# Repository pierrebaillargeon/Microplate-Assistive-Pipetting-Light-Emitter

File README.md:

# Microplate Assistive Pipetting Light Emitter

The contents of this repository represent the design files and code needed to reproduce the electronics, firmware and GUI interface for the Microplate Assistive Pipetting Light Emitter. 

A manuscript describing the design and usage of this light guide has been published in the <A href="https://journals.sagepub.com/doi/full/10.1177/2472630318822476">SLAS Technology journal</A> and presented at SLAS 2019 as part of a presentation titled <A href="https://www.pathlms.com/slas/courses/10547/video_presentations/127546">'A longitudinal analysis over 10 years of enabling technologies for early drug discovery using open source tools'</a>.

If you are interested in purchasing preassembled illumination panels, as opposed to assembling them by hand, they are available on the <a href="https://www.tindie.com/stores/Maplebear/">Maplebear Electronics Tindie store</a>.

<A href="https://raw.githubusercontent.com/pierrebaillargeon/Microplate-Assistive-Pipetting-Light-Emitter/master/Electronics/Documentation/96-well_RGB_light_Guide_v1.0-with_microplate.jpg"></a>
  
<A href="https://raw.githubusercontent.com/pierrebaillargeon/Microplate-Assistive-Pipetting-Light-Emitter/master/Electronics/Documentation/96-well_RGB_light_guide_v1.3-prototype_PCB.png"></a>
  
<A href="https://raw.githubusercontent.com/pierrebaillargeon/Microplate-Assistive-Pipetting-Light-Emitter/master/Electronics/Documentation/384-well_RGB_light_guide_v1.1.png"></a>

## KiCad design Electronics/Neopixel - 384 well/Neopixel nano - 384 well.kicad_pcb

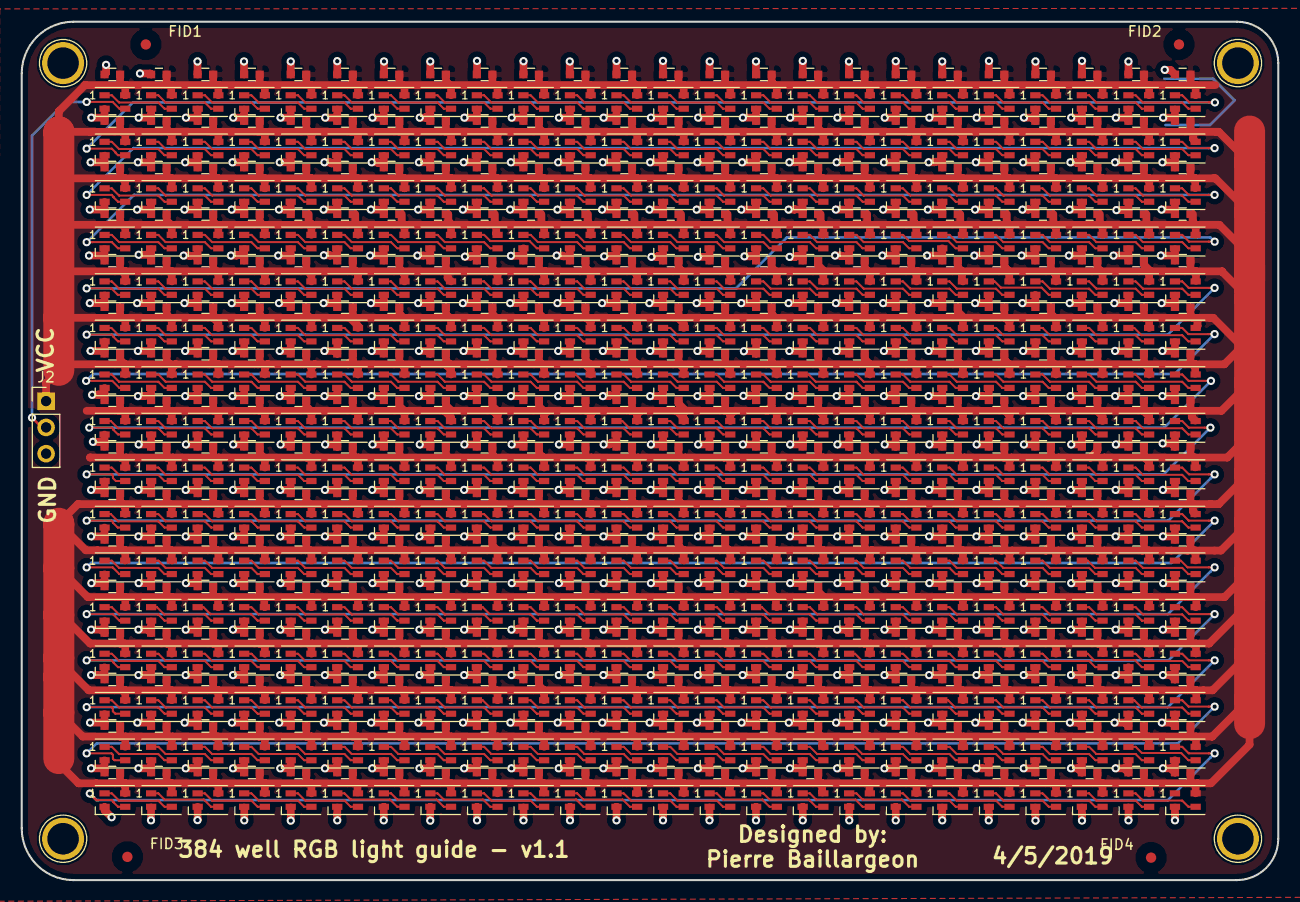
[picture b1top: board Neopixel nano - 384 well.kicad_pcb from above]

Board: 2 copper layers, 121.5 x 83.0 mm, 773 parts (0 on the bottom side), 386 nets.

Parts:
C1, C2, C3, C4, C5, C6, C7, C8, C9, C10, C11, C12, C13, C14, C15, C16, C17, C18, C19, C20, C21, C22, C23, C24, C25, C26, C27, C28, C29, C30, C31, C32, C33, C34, C35, C36, C37, C38, C39, C40, C41, C42, C43, C44, C45, C46, C47, C48, C49, C50, C51, C52, C53, C54, C55, C56, C57, C58, C59, C60, C61, C62, C63, C64, C65, C66, C67, C68, C69, C70, C71, C72, C73, C74, C75, C76, C77, C78, C79, C80, C81, C82, C83, C84, C85, C86, C87, C88, C89, C90, C91, C92, C93, C94, C95, C96, C97, C98, C99, C100, C101, C102, C103, C104, C105, C106, C107, C108, C109, C110, C111, C112, C113, C114, C115, C116, C117, C118, C119, C120, C121, C122, C123, C124, C125, C126, C127, C128, C129, C130, C131, C132, C133, C134, C135, C136, C137, C138, C139, C140, C141, C142, C143, C144, C145, C146, C147, C148, C149, C150, C151, C152, C153, C154, C155, C156, C157, C158, C159, C160, C161, C162, C163, C164, C165, C166, C167, C168, C169, C170, C171, C172, C173, C174, C175, C176, C177, C178, C179, C180, C181, C182, C183, C184, C185, C186, C187, C188, C189, C190, C191, C192, C193, C194, C195, C196, C197, C198, C199, C200, C201, C202, C203, C204, C205, C206, C207, C208, C209, C210, C211, C212, C213, C214, C215, C216, C217, C218, C219, C220, C221, C222, C223, C224, C225, C226, C227, C228, C229, C230, C231, C232, C233, C234, C235, C236, C237, C238, C239, C240, C241, C242, C243, C244, C245, C246, C247, C248, C249, C250, C251, C252, C253, C254, C255, C256, C257, C258, C259, C260, C261, C262, C263, C264, C265, C266, C267, C268, C269, C270, C271, C272, C273, C274, C275, C276, C277, C278, C279, C280, C281, C282, C283, C284, C285, C286, C287, C288, C289, C290, C291, C292, C293, C294, C295, C296, C297, C298, C299, C300, C301, C302, C303, C304, C305, C306, C307, C308, C309, C310, C311, C312, C313, C314, C315, C316, C317, C318, C319, C320, C321, C322, C323, C324, C325, C326, C327, C328, C329, C330, C331, C332, C333, C334, C335, C336, C337, C338, C339, C340, C341, C342, C343, C344, C345, C346, C347, C348, C349, C350, C351, C352, C353, C354, C355, C356, C357, C358, C359, C360, C361, C362, C363, C364, C365, C366, C367, C368, C369, C370, C371, C372, C373, C374, C375, C376, C377, C378, C379, C380, C381, C382, C383, C384: CAP; C_0603
D1, D2, D3, D4, D5, D6, D7, D8, D9, D10, D11, D12, D13, D14, D15, D16, D17, D18, D19, D20, D21, D22, D23, D24, D25, D26, D27, D28, D29, D30, D31, D32, D33, D34, D35, D36, D37, D38, D39, D40, D41, D42, D43, D44, D45, D46, D47, D48, D49, D50, D51, D52, D53, D54, D55, D56, D57, D58, D59, D60, D61, D62, D63, D64, D65, D66, D67, D68, D69, D70, D71, D72, D73, D74, D75, D76, D77, D78, D79, D80, D81, D82, D83, D84, D85, D86, D87, D88, D89, D90, D91, D92, D93, D94, D95, D96, D97, D98, D99, D100, D101, D102, D103, D104, D105, D106, D107, D108, D109, D110, D111, D112, D113, D114, D115, D116, D117, D118, D119, D120, D121, D122, D123, D124, D125, D126, D127, D128, D129, D130, D131, D132, D133, D134, D135, D136, D137, D138, D139, D140, D141, D142, D143, D144, D145, D146, D147, D148, D149, D150, D151, D152, D153, D154, D155, D156, D157, D158, D159, D160, D161, D162, D163, D164, D165, D166, D167, D168, D169, D170, D171, D172, D173, D174, D175, D176, D177, D178, D179, D180, D181, D182, D183, D184, D185, D186, D187, D188, D189, D190, D191, D192, D193, D194, D195, D196, D197, D198, D199, D200, D201, D202, D203, D204, D205, D206, D207, D208, D209, D210, D211, D212, D213, D214, D215, D216, D217, D218, D219, D220, D221, D222, D223, D224, D225, D226, D227, D228, D229, D230, D231, D232, D233, D234, D235, D236, D237, D238, D239, D240, D241, D242, D243, D244, D245, D246, D247, D248, D249, D250, D251, D252, D253, D254, D255, D256, D257, D258, D259, D260, D261, D262, D263, D264, D265, D266, D267, D268, D269, D270, D271, D272, D273, D274, D275, D276, D277, D278, D279, D280, D281, D282, D283, D284, D285, D286, D287, D288, D289, D290, D291, D292, D293, D294, D295, D296, D297, D298, D299, D300, D301, D302, D303, D304, D305, D306, D307, D308, D309, D310, D311, D312, D313, D314, D315, D316, D317, D318, D319, D320, D321, D322, D323, D324, D325, D326, D327, D328, D329, D330, D331, D332, D333, D334, D335, D336, D337, D338, D339, D340, D341, D342, D343, D344, D345, D346, D347, D348, D349, D350, D351, D352, D353, D354, D355, D356, D357, D358, D359, D360, D361, D362, D363, D364, D365, D366, D367, D368, D369, D370, D371, D372, D373, D374, D375, D376, D377, D378, D379, D380, D381, D382, D383, D384: SK6805; LED_SK6805_PLCC4_2.4x2.7mm_P1.3mm
FID1, FID2, FID3, FID4: Fiducial_1mm_Mask3mm
J2: Conn_01x03_Male; Pin_Header_Straight_1x03_Pitch2.54mm

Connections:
GND: C1.2, C2.2, C3.2, C4.2, C5.2, C6.2, C7.2, C8.2, C9.2, C10.2, C11.2, C12.2, C13.2, C14.2, C15.2, C16.2, C17.2, C18.2, C19.2, C20.2, C21.2, C22.2, C23.2, C24.2, C25.2, C26.2, C27.2, C28.2, C29.2, C30.2, C31.2, C32.2, C33.2, C34.2, C35.2, C36.2, C37.2, C38.2, C39.2, C40.2, C41.2, C42.2, C43.2, C44.2, C45.2, C46.2, C47.2, C48.2, C49.2, C50.2, C51.2, C52.2, C53.2, C54.2, C55.2, C56.2, C57.2, C58.2, C59.2, C60.2, C61.2, C62.2, C63.2, C64.2, C65.2, C66.2, C67.2, C68.2, C69.2, C70.2, C71.2, C72.2, C73.2, C74.2, C75.2, C76.2, C77.2, C78.2, C79.2, C80.2, C81.2, C82.2, C83.2, C84.2, C85.2, C86.2, C87.2, C88.2, C89.2, C90.2, C91.2, C92.2, C93.2, C94.2, C95.2, C96.2, C97.2, C98.2, C99.2, C100.2, C101.2, C102.2, C103.2, C104.2, C105.2, C106.2, C107.2, C108.2, C109.2, C110.2, C111.2, C112.2, C113.2, C114.2, C115.2, C116.2, C117.2, C118.2, C119.2, C120.2, C121.2, C122.2, C123.2, C124.2, C125.2, C126.2, C127.2, C128.2, C129.2, C130.2, C131.2, C132.2, C133.2, C134.2, C135.2, C136.2, C137.2, C138.2, C139.2, C140.2, C141.2, C142.2, C143.2, C144.2, C145.2, C146.2, C147.2, C148.2, C149.2, C150.2, C151.2, C152.2, C153.2, C154.2, C155.2, C156.2, C157.2, C158.2, C159.2, C160.2, C161.2, C162.2, C163.2, C164.2, C165.2, C166.2, C167.2, C168.2, C169.2, C170.2, C171.2, C172.2, C173.2, C174.2, C175.2, C176.2, C177.2, C178.2, C179.2, C180.2, C181.2, C182.2, C183.2, C184.2, C185.2, C186.2, C187.2, C188.2, C189.2, C190.2, C191.2, C192.2, C193.2, C194.2, C195.2, C196.2, C197.2, C198.2, C199.2, C200.2, C201.2, C202.2, C203.2, C204.2, C205.2, C206.2, C207.2, C208.2, C209.2, C210.2, C211.2, C212.2, C213.2, C214.2, C215.2, C216.2, C217.2, C218.2, C219.2, C220.2, C221.2, C222.2, C223.2, C224.2, C225.2, C226.2, C227.2, C228.2, C229.2, C230.2, C231.2, C232.2, C233.2, C234.2, C235.2, C236.2, C237.2, C238.2, C239.2, C240.2, C241.2, C242.2, C243.2, C244.2, C245.2, C246.2, C247.2, C248.2, C249.2, C250.2, C251.2, C252.2, C253.2, C254.2, C255.2, C256.2, C257.2, C258.2, C259.2, C260.2, C261.2, C262.2, C263.2, C264.2, C265.2, C266.2, C267.2, C268.2, C269.2, C270.2, C271.2, C272.2, C273.2, C274.2, C275.2, C276.2, C277.2, C278.2, C279.2, C280.2, C281.2, C282.2, C283.2, C284.2, C285.2, C286.2, C287.2, C288.2, C289.2, C290.2, C291.2, C292.2, C293.2, C294.2, C295.2, C296.2, C297.2, C298.2, C299.2, C300.2, C301.2, C302.2, C303.2, C304.2, C305.2, C306.2, C307.2, C308.2, C309.2, C310.2, C311.2, C312.2, C313.2, C314.2, C315.2, C316.2, C317.2, C318.2, C319.2, C320.2, C321.2, C322.2, C323.2, C324.2, C325.2, C326.2, C327.2, C328.2, C329.2, C330.2, C331.2, C332.2, C333.2, C334.2, C335.2, C336.2, C337.2, C338.2, C339.2, C340.2, C341.2, C342.2, C343.2, C344.2, C345.2, C346.2, C347.2, C348.2, C349.2, C350.2, C351.2, C352.2, C353.2, C354.2, C355.2, C356.2, C357.2, C358.2, C359.2, C360.2, C361.2, C362.2, C363.2, C364.2, C365.2, C366.2, C367.2, C368.2, C369.2, C370.2, C371.2, C372.2, C373.2, C374.2, C375.2, C376.2, C377.2, C378.2, C379.2, C380.2, C381.2, C382.2, C383.2, C384.2, D1.2, D2.2, D3.2, D4.2, D5.2, D6.2, D7.2, D8.2, D9.2, D10.2, D11.2, D12.2, D13.2, D14.2, D15.2, D16.2, D17.2, D18.2, D19.2, D20.2, D21.2, D22.2, D23.2, D24.2, D25.2, D26.2, D27.2, D28.2, D29.2, D30.2, D31.2, D32.2, D33.2, D34.2, D35.2, D36.2, D37.2, D38.2, D39.2, D40.2, D41.2, D42.2, D43.2, D44.2, D45.2, D46.2, D47.2, D48.2, D49.2, D50.2, D51.2, D52.2, D53.2, D54.2, D55.2, D56.2, D57.2, D58.2, D59.2, D60.2, D61.2, D62.2, D63.2, D64.2, D65.2, D66.2, D67.2, D68.2, D69.2, D70.2, D71.2, D72.2, D73.2, D74.2, D75.2, D76.2, D77.2, D78.2, D79.2, D80.2, D81.2, D82.2, D83.2, D84.2, D85.2, D86.2, D87.2, D88.2, D89.2, D90.2, D91.2, D92.2, D93.2, D94.2, D95.2, D96.2, D97.2, D98.2, D99.2, D100.2, D101.2, D102.2, D103.2, D104.2, D105.2, D106.2, D107.2, D108.2, D109.2, D110.2, D111.2, D112.2, D113.2, D114.2, D115.2, D116.2, D117.2, D118.2, D119.2, D120.2, D121.2, D122.2, D123.2, D124.2, D125.2, D126.2, D127.2, D128.2, D129.2, D130.2, D131.2, D132.2, D133.2, D134.2, D135.2, D136.2, D137.2, D138.2, D139.2, D140.2, D141.2, D142.2, D143.2, D144.2, D145.2, D146.2, D147.2, D148.2, D149.2, D150.2, D151.2, D152.2, D153.2, D154.2, D155.2, D156.2, D157.2, D158.2, D159.2, D160.2, D161.2, D162.2, D163.2, D164.2, D165.2, D166.2, D167.2, D168.2, D169.2, D170.2, D171.2, D172.2, D173.2, D174.2, D175.2, D176.2, D177.2, D178.2, D179.2, D180.2, D181.2, D182.2, D183.2, D184.2, D185.2, D186.2, D187.2, D188.2, D189.2, D190.2, D191.2, D192.2, D193.2, D194.2, D195.2, D196.2, D197.2, D198.2, D199.2, D200.2, D201.2, D202.2, D203.2, D204.2, D205.2, D206.2, D207.2, D208.2, D209.2, D210.2, D211.2, D212.2, D213.2, D214.2, D215.2, D216.2, D217.2, D218.2, D219.2, D220.2, D221.2, D222.2, D223.2, D224.2, D225.2, D226.2, D227.2, D228.2, D229.2, D230.2, D231.2, D232.2, D233.2, D234.2, D235.2, D236.2, D237.2, D238.2, D239.2, D240.2, D241.2, D242.2, D243.2, D244.2, D245.2, D246.2, D247.2, D248.2, D249.2, D250.2, D251.2, D252.2, D253.2, D254.2, D255.2, D256.2, D257.2, D258.2, D259.2, D260.2, D261.2, D262.2, D263.2, D264.2, D265.2, D266.2, D267.2, D268.2, D269.2, D270.2, D271.2, D272.2, D273.2, D274.2, D275.2, D276.2, D277.2, D278.2, D279.2, D280.2, D281.2, D282.2, D283.2, D284.2, D285.2, D286.2, D287.2, D288.2, D289.2, D290.2, D291.2, D292.2, D293.2, D294.2, D295.2, D296.2, D297.2, D298.2, D299.2, D300.2, D301.2, D302.2, D303.2, D304.2, D305.2, D306.2, D307.2, D308.2, D309.2, D310.2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
unnamed: D1.1, D2.3
unnamed: D1.3, J2.2
unnamed: D2.1, D3.3
unnamed: D3.1, D4.3
unnamed: D4.1, D5.3
unnamed: D5.1, D6.3
unnamed: D6.1, D7.3
unnamed: D7.1, D8.3
unnamed: D8.1, D9.3
unnamed: D10.1, D11.3
unnamed: D9.1, D10.3
unnamed: D11.1, D12.3
unnamed: D12.1, D13.3
unnamed: D13.1, D14.3
unnamed: D14.1, D15.3
unnamed: D15.1, D16.3
unnamed: D16.1, D17.3
unnamed: D17.1, D18.3
unnamed: D18.1, D19.3
unnamed: D19.1, D20.3
unnamed: D20.1, D21.3
unnamed: D21.1, D22.3
unnamed: D22.1, D23.3
unnamed: D23.1, D24.3
unnamed: D24.1, D25.3
unnamed: D25.1, D26.3
unnamed: D26.1, D27.3
unnamed: D27.1, D28.3
unnamed: D28.1, D29.3
unnamed: D29.1, D30.3
unnamed: D30.1, D31.3
unnamed: D31.1, D32.3
unnamed: D32.1, D33.3
unnamed: D33.1, D34.3
unnamed: D34.1, D35.3
unnamed: D35.1, D36.3
unnamed: D36.1, D37.3
unnamed: D37.1, D38.3
unnamed: D38.1, D39.3
unnamed: D39.1, D40.3
unnamed: D40.1, D41.3
unnamed: D41.1, D42.3
unnamed: D42.1, D43.3
unnamed: D43.1, D44.3
unnamed: D44.1, D45.3
unnamed: D45.1, D46.3
unnamed: D46.1, D47.3
unnamed: D47.1, D48.3
unnamed: D48.1, D49.3
unnamed: D49.1, D50.3
unnamed: D50.1, D51.3
unnamed: D51.1, D52.3
unnamed: D52.1, D53.3
unnamed: D53.1, D54.3
unnamed: D54.1, D55.3
unnamed: D55.1, D56.3
unnamed: D56.1, D57.3
unnamed: D57.1, D58.3
unnamed: D58.1, D59.3
unnamed: D59.1, D60.3
unnamed: D60.1, D61.3
unnamed: D61.1, D62.3
unnamed: D62.1, D63.3
unnamed: D63.1, D64.3
unnamed: D64.1, D65.3
unnamed: D65.1, D66.3
unnamed: D66.1, D67.3
unnamed: D67.1, D68.3
unnamed: D68.1, D69.3
unnamed: D69.1, D70.3
unnamed: D70.1, D71.3
unnamed: D71.1, D72.3
unnamed: D72.1, D73.3
unnamed: D73.1, D74.3
unnamed: D74.1, D75.3
unnamed: D75.1, D76.3
unnamed: D76.1, D77.3
unnamed: D77.1, D78.3
unnamed: D78.1, D79.3
unnamed: D79.1, D80.3
unnamed: D80.1, D81.3
unnamed: D81.1, D82.3
unnamed: D82.1, D83.3
unnamed: D83.1, D84.3
unnamed: D84.1, D85.3
unnamed: D85.1, D86.3
unnamed: D86.1, D87.3
unnamed: D87.1, D88.3
unnamed: D88.1, D89.3
unnamed: D89.1, D90.3
unnamed: D90.1, D91.3
unnamed: D91.1, D92.3
unnamed: D92.1, D93.3
unnamed: D93.1, D94.3
unnamed: D94.1, D95.3
unnamed: D95.1, D96.3
unnamed: D96.1, D97.3
unnamed: D97.1, D98.3
unnamed: D98.1, D99.3
unnamed: D100.1, D101.3
unnamed: D99.1, D100.3
unnamed: D101.1, D102.3
unnamed: D102.1, D103.3
unnamed: D103.1, D104.3
unnamed: D104.1, D105.3
unnamed: D105.1, D106.3
unnamed: D106.1, D107.3
unnamed: D107.1, D108.3
unnamed: D108.1, D109.3
unnamed: D109.1, D110.3
unnamed: D110.1, D111.3
unnamed: D111.1, D112.3
unnamed: D112.1, D113.3
unnamed: D113.1, D114.3
unnamed: D114.1, D115.3
unnamed: D115.1, D116.3
unnamed: D116.1, D117.3
unnamed: D117.1, D118.3
unnamed: D118.1, D119.3
unnamed: D119.1, D120.3
unnamed: D120.1, D121.3
unnamed: D121.1, D122.3
unnamed: D122.1, D123.3
unnamed: D123.1, D124.3
unnamed: D124.1, D125.3
unnamed: D125.1, D126.3
unnamed: D126.1, D127.3
unnamed: D127.1, D128.3
unnamed: D128.1, D129.3
unnamed: D129.1, D130.3
unnamed: D130.1, D131.3
unnamed: D131.1, D132.3
unnamed: D132.1, D133.3
unnamed: D133.1, D134.3
unnamed: D134.1, D135.3
unnamed: D135.1, D136.3
unnamed: D136.1, D137.3
unnamed: D137.1, D138.3
unnamed: D138.1, D139.3
unnamed: D139.1, D140.3
unnamed: D140.1, D141.3
unnamed: D141.1, D142.3
unnamed: D142.1, D143.3
unnamed: D143.1, D144.3
unnamed: D144.1, D145.3
unnamed: D145.1, D146.3
unnamed: D146.1, D147.3
unnamed: D147.1, D148.3
unnamed: D148.1, D149.3
unnamed: D149.1, D150.3
unnamed: D150.1, D151.3
unnamed: D151.1, D152.3
unnamed: D152.1, D153.3
unnamed: D153.1, D154.3
unnamed: D154.1, D155.3
unnamed: D155.1, D156.3
unnamed: D156.1, D157.3
unnamed: D157.1, D158.3
unnamed: D158.1, D159.3
unnamed: D159.1, D160.3
unnamed: D160.1, D161.3
unnamed: D161.1, D162.3
unnamed: D162.1, D163.3
unnamed: D163.1, D164.3
unnamed: D164.1, D165.3
unnamed: D165.1, D166.3
unnamed: D166.1, D167.3
unnamed: D167.1, D168.3
unnamed: D168.1, D169.3
unnamed: D169.1, D170.3
unnamed: D170.1, D171.3
unnamed: D171.1, D172.3
unnamed: D172.1, D173.3
unnamed: D173.1, D174.3
unnamed: D174.1, D175.3
unnamed: D175.1, D176.3
unnamed: D176.1, D177.3
unnamed: D177.1, D178.3
unnamed: D178.1, D179.3
unnamed: D179.1, D180.3
unnamed: D180.1, D181.3
unnamed: D181.1, D182.3
unnamed: D182.1, D183.3
unnamed: D183.1, D184.3
unnamed: D184.1, D185.3
unnamed: D185.1, D186.3
unnamed: D186.1, D187.3
unnamed: D187.1, D188.3
unnamed: D188.1, D189.3
unnamed: D189.1, D190.3
unnamed: D190.1, D191.3
unnamed: D191.1, D192.3
unnamed: D192.1, D193.3
unnamed: D193.1, D194.3
unnamed: D194.1, D195.3
unnamed: D195.1, D196.3
unnamed: D196.1, D197.3
unnamed: D197.1, D198.3
unnamed: D198.1, D199.3
unnamed: D199.1, D200.3
unnamed: D200.1, D201.3
unnamed: D201.1, D202.3
unnamed: D202.1, D203.3
unnamed: D203.1, D204.3
unnamed: D204.1, D205.3
unnamed: D205.1, D206.3
unnamed: D206.1, D207.3
unnamed: D207.1, D208.3
unnamed: D208.1, D209.3
unnamed: D209.1, D210.3
unnamed: D210.1, D211.3
unnamed: D211.1, D212.3
unnamed: D212.1, D213.3
unnamed: D213.1, D214.3
unnamed: D214.1, D215.3
unnamed: D215.1, D216.3
unnamed: D216.1, D217.3
unnamed: D217.1, D218.3
unnamed: D218.1, D219.3
unnamed: D219.1, D220.3
unnamed: D220.1, D221.3
unnamed: D221.1, D222.3
unnamed: D222.1, D223.3
unnamed: D223.1, D224.3
unnamed: D224.1, D225.3
unnamed: D225.1, D226.3
unnamed: D226.1, D227.3
unnamed: D227.1, D228.3
unnamed: D228.1, D229.3
unnamed: D229.1, D230.3
unnamed: D230.1, D231.3
unnamed: D231.1, D232.3
unnamed: D232.1, D233.3
unnamed: D233.1, D234.3
unnamed: D234.1, D235.3
unnamed: D235.1, D236.3
unnamed: D236.1, D237.3
unnamed: D237.1, D238.3
unnamed: D238.1, D239.3
unnamed: D239.1, D240.3
unnamed: D240.1, D241.3
unnamed: D241.1, D242.3
unnamed: D242.1, D243.3
unnamed: D243.1, D244.3
unnamed: D244.1, D245.3
unnamed: D245.1, D246.3
unnamed: D246.1, D247.3
unnamed: D247.1, D248.3
unnamed: D248.1, D249.3
unnamed: D249.1, D250.3
unnamed: D250.1, D251.3
unnamed: D251.1, D252.3
unnamed: D252.1, D253.3
unnamed: D253.1, D254.3
unnamed: D254.1, D255.3
unnamed: D255.1, D256.3
unnamed: D256.1, D257.3
unnamed: D257.1, D258.3
unnamed: D258.1, D259.3
unnamed: D259.1, D260.3
unnamed: D260.1, D261.3
unnamed: D261.1, D262.3
unnamed: D262.1, D263.3
unnamed: D263.1, D264.3
unnamed: D264.1, D265.3
unnamed: D265.1, D266.3
unnamed: D266.1, D267.3
unnamed: D267.1, D268.3
unnamed: D268.1, D269.3
unnamed: D269.1, D270.3
unnamed: D270.1, D271.3
unnamed: D271.1, D272.3
unnamed: D272.1, D273.3
unnamed: D273.1, D274.3
unnamed: D274.1, D275.3
unnamed: D275.1, D276.3
unnamed: D276.1, D277.3
unnamed: D277.1, D278.3
unnamed: D278.1, D279.3
unnamed: D279.1, D280.3
unnamed: D280.1, D281.3
unnamed: D281.1, D282.3
unnamed: D282.1, D283.3
unnamed: D283.1, D284.3
unnamed: D284.1, D285.3
unnamed: D285.1, D286.3
unnamed: D286.1, D287.3
unnamed: D287.1, D288.3
unnamed: D288.1, D289.3
unnamed: D289.1, D290.3
unnamed: D290.1, D291.3
unnamed: D291.1, D292.3
unnamed: D292.1, D293.3
unnamed: D293.1, D294.3
unnamed: D294.1, D295.3
unnamed: D295.1, D296.3
unnamed: D296.1, D297.3
unnamed: D297.1, D298.3
unnamed: D298.1, D299.3
unnamed: D299.1, D300.3
unnamed: D300.1, D301.3
unnamed: D301.1, D302.3
unnamed: D302.1, D303.3
unnamed: D303.1, D304.3
unnamed: D304.1, D305.3
unnamed: D305.1, D306.3
unnamed: D306.1, D307.3
unnamed: D307.1, D308.3
unnamed: D308.1, D309.3
unnamed: D309.1, D310.3
unnamed: D310.1, D311.3
unnamed: D311.1, D312.3
unnamed: D312.1, D313.3
unnamed: D313.1, D314.3
unnamed: D314.1, D315.3
unnamed: D315.1, D316.3
unnamed: D316.1, D317.3
unnamed: D317.1, D318.3
unnamed: D318.1, D319.3
unnamed: D319.1, D320.3
unnamed: D320.1, D321.3
unnamed: D321.1, D322.3
unnamed: D322.1, D323.3
unnamed: D323.1, D324.3
unnamed: D324.1, D325.3
unnamed: D325.1, D326.3
unnamed: D326.1, D327.3
unnamed: D327.1, D328.3
unnamed: D328.1, D329.3
unnamed: D329.1, D330.3
unnamed: D330.1, D331.3
unnamed: D331.1, D332.3
unnamed: D332.1, D333.3
unnamed: D333.1, D334.3
unnamed: D334.1, D335.3
unnamed: D335.1, D336.3
unnamed: D336.1, D337.3
unnamed: D337.1, D338.3
unnamed: D338.1, D339.3
unnamed: D339.1, D340.3
unnamed: D340.1, D341.3
unnamed: D341.1, D342.3
unnamed: D342.1, D343.3
unnamed: D343.1, D344.3
unnamed: D344.1, D345.3
unnamed: D345.1, D346.3
unnamed: D346.1, D347.3
unnamed: D347.1, D348.3
unnamed: D348.1, D349.3
unnamed: D349.1, D350.3
unnamed: D350.1, D351.3
unnamed: D351.1, D352.3
unnamed: D352.1, D353.3
unnamed: D353.1, D354.3
unnamed: D354.1, D355.3
unnamed: D355.1, D356.3
unnamed: D356.1, D357.3
unnamed: D357.1, D358.3
unnamed: D358.1, D359.3
unnamed: D359.1, D360.3
unnamed: D360.1, D361.3
unnamed: D361.1, D362.3
unnamed: D362.1, D363.3
unnamed: D363.1, D364.3
unnamed: D364.1, D365.3
unnamed: D365.1, D366.3
unnamed: D366.1, D367.3
unnamed: D367.1, D368.3
unnamed: D368.1, D369.3
unnamed: D369.1, D370.3
unnamed: D370.1, D371.3
unnamed: D371.1, D372.3
unnamed: D372.1, D373.3
unnamed: D373.1, D374.3
unnamed: D374.1, D375.3
unnamed: D375.1, D376.3
unnamed: D376.1, D377.3
unnamed: D377.1, D378.3
unnamed: D378.1, D379.3
unnamed: D379.1, D380.3
unnamed: D380.1, D381.3
unnamed: D381.1, D382.3
unnamed: D382.1, D383.3
unnamed: D383.1, D384.3
VCC: C1.1, C2.1, C3.1, C4.1, C5.1, C6.1, C7.1, C8.1, C9.1, C10.1, C11.1, C12.1, C13.1, C14.1, C15.1, C16.1, C17.1, C18.1, C19.1, C20.1, C21.1, C22.1, C23.1, C24.1, C25.1, C26.1, C27.1, C28.1, C29.1, C30.1, C31.1, C32.1, C33.1, C34.1, C35.1, C36.1, C37.1, C38.1, C39.1, C40.1, C41.1, C42.1, C43.1, C44.1, C45.1, C46.1, C47.1, C48.1, C49.1, C50.1, C51.1, C52.1, C53.1, C54.1, C55.1, C56.1, C57.1, C58.1, C59.1, C60.1, C61.1, C62.1, C63.1, C64.1, C65.1, C66.1, C67.1, C68.1, C69.1, C70.1, C71.1, C72.1, C73.1, C74.1, C75.1, C76.1, C77.1, C78.1, C79.1, C80.1, C81.1, C82.1, C83.1, C84.1, C85.1, C86.1, C87.1, C88.1, C89.1, C90.1, C91.1, C92.1, C93.1, C94.1, C95.1, C96.1, C97.1, C98.1, C99.1, C100.1, C101.1, C102.1, C103.1, C104.1, C105.1, C106.1, C107.1, C108.1, C109.1, C110.1, C111.1, C112.1, C113.1, C114.1, C115.1, C116.1, C117.1, C118.1, C119.1, C120.1, C121.1, C122.1, C123.1, C124.1, C125.1, C126.1, C127.1, C128.1, C129.1, C130.1, C131.1, C132.1, C133.1, C134.1, C135.1, C136.1, C137.1, C138.1, C139.1, C140.1, C141.1, C142.1, C143.1, C144.1, C145.1, C146.1, C147.1, C148.1, C149.1, C150.1, C151.1, C152.1, C153.1, C154.1, C155.1, C156.1, C157.1, C158.1, C159.1, C160.1, C161.1, C162.1, C163.1, C164.1, C165.1, C166.1, C167.1, C168.1, C169.1, C170.1, C171.1, C172.1, C173.1, C174.1, C175.1, C176.1, C177.1, C178.1, C179.1, C180.1, C181.1, C182.1, C183.1, C184.1, C185.1, C186.1, C187.1, C188.1, C189.1, C190.1, C191.1, C192.1, C193.1, C194.1, C195.1, C196.1, C197.1, C198.1, C199.1, C200.1, C201.1, C202.1, C203.1, C204.1, C205.1, C206.1, C207.1, C208.1, C209.1, C210.1, C211.1, C212.1, C213.1, C214.1, C215.1, C216.1, C217.1, C218.1, C219.1, C220.1, C221.1, C222.1, C223.1, C224.1, C225.1, C226.1, C227.1, C228.1, C229.1, C230.1, C231.1, C232.1, C233.1, C234.1, C235.1, C236.1, C237.1, C238.1, C239.1, C240.1, C241.1, C242.1, C243.1, C244.1, C245.1, C246.1, C247.1, C248.1, C249.1, C250.1, C251.1, C252.1, C253.1, C254.1, C255.1, C256.1, C257.1, C258.1, C259.1, C260.1, C261.1, C262.1, C263.1, C264.1, C265.1, C266.1, C267.1, C268.1, C269.1, C270.1, C271.1, C272.1, C273.1, C274.1, C275.1, C276.1, C277.1, C278.1, C279.1, C280.1, C281.1, C282.1, C283.1, C284.1, C285.1, C286.1, C287.1, C288.1, C289.1, C290.1, C291.1, C292.1, C293.1, C294.1, C295.1, C296.1, C297.1, C298.1, C299.1, C300.1, C301.1, C302.1, C303.1, C304.1, C305.1, C306.1, C307.1, C308.1, C309.1, C310.1, C311.1, C312.1, C313.1, C314.1, C315.1, C316.1, C317.1, C318.1, C319.1, C320.1, C321.1, C322.1, C323.1, C324.1, C325.1, C326.1, C327.1, C328.1, C329.1, C330.1, C331.1, C332.1, C333.1, C334.1, C335.1, C336.1, C337.1, C338.1, C339.1, C340.1, C341.1, C342.1, C343.1, C344.1, C345.1, C346.1, C347.1, C348.1, C349.1, C350.1, C351.1, C352.1, C353.1, C354.1, C355.1, C356.1, C357.1, C358.1, C359.1, C360.1, C361.1, C362.1, C363.1, C364.1, C365.1, C366.1, C367.1, C368.1, C369.1, C370.1, C371.1, C372.1, C373.1, C374.1, C375.1, C376.1, C377.1, C378.1, C379.1, C380.1, C381.1, C382.1, C383.1, C384.1, D1.4, D2.4, D3.4, D4.4, D5.4, D6.4, D7.4, D8.4, D9.4, D10.4, D11.4, D12.4, D13.4, D14.4, D15.4, D16.4, D17.4, D18.4, D19.4, D20.4, D21.4, D22.4, D23.4, D24.4, D25.4, D26.4, D27.4, D28.4, D29.4, D30.4, D31.4, D32.4, D33.4, D34.4, D35.4, D36.4, D37.4, D38.4, D39.4, D40.4, D41.4, D42.4, D43.4, D44.4, D45.4, D46.4, D47.4, D48.4, D49.4, D50.4, D51.4, D52.4, D53.4, D54.4, D55.4, D56.4, D57.4, D58.4, D59.4, D60.4, D61.4, D62.4, D63.4, D64.4, D65.4, D66.4, D67.4, D68.4, D69.4, D70.4, D71.4, D72.4, D73.4, D74.4, D75.4, D76.4, D77.4, D78.4, D79.4, D80.4, D81.4, D82.4, D83.4, D84.4, D85.4, D86.4, D87.4, D88.4, D89.4, D90.4, D91.4, D92.4, D93.4, D94.4, D95.4, D96.4, D97.4, D98.4, D99.4, D100.4, D101.4, D102.4, D103.4, D104.4, D105.4, D106.4, D107.4, D108.4, D109.4, D110.4, D111.4, D112.4, D113.4, D114.4, D115.4, D116.4, D117.4, D118.4, D119.4, D120.4, D121.4, D122.4, D123.4, D124.4, D125.4, D126.4, D127.4, D128.4, D129.4, D130.4, D131.4, D132.4, D133.4, D134.4, D135.4, D136.4, D137.4, D138.4, D139.4, D140.4, D141.4, D142.4, D143.4, D144.4, D145.4, D146.4, D147.4, D148.4, D149.4, D150.4, D151.4, D152.4, D153.4, D154.4, D155.4, D156.4, D157.4, D158.4, D159.4, D160.4, D161.4, D162.4, D163.4, D164.4, D165.4, D166.4, D167.4, D168.4, D169.4, D170.4, D171.4, D172.4, D173.4, D174.4, D175.4, D176.4, D177.4, D178.4, D179.4, D180.4, D181.4, D182.4, D183.4, D184.4, D185.4, D186.4, D187.4, D188.4, D189.4, D190.4, D191.4, D192.4, D193.4, D194.4, D195.4, D196.4, D197.4, D198.4, D199.4, D200.4, D201.4, D202.4, D203.4, D204.4, D205.4, D206.4, D207.4, D208.4, D209.4, D210.4, D211.4, D212.4, D213.4, D214.4, D215.4, D216.4, D217.4, D218.4, D219.4, D220.4, D221.4, D222.4, D223.4, D224.4, D225.4, D226.4, D227.4, D228.4, D229.4, D230.4, D231.4, D232.4, D233.4, D234.4, D235.4, D236.4, D237.4, D238.4, D239.4, D240.4, D241.4, D242.4, D243.4, D244.4, D245.4, D246.4, D247.4, D248.4, D249.4, D250.4, D251.4, D252.4, D253.4, D254.4, D255.4, D256.4, D257.4, D258.4, D259.4, D260.4, D261.4, D262.4, D263.4, D264.4, D265.4, D266.4, D267.4, D268.4, D269.4, D270.4, D271.4, D272.4, D273.4, D274.4, D275.4, D276.4, D277.4, D278.4, D279.4, D280.4, D281.4, D282.4, D283.4, D284.4, D285.4, D286.4, D287.4, D288.4, D289.4, D290.4, D291.4, D292.4, D293.4, D294.4, D295.4, D296.4, D297.4, D298.4, D299.4, D300.4, D301.4, D302.4, D303.4, D304.4, D305.4, D306.4, D307.4, D308.4, D309.4, D310.4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

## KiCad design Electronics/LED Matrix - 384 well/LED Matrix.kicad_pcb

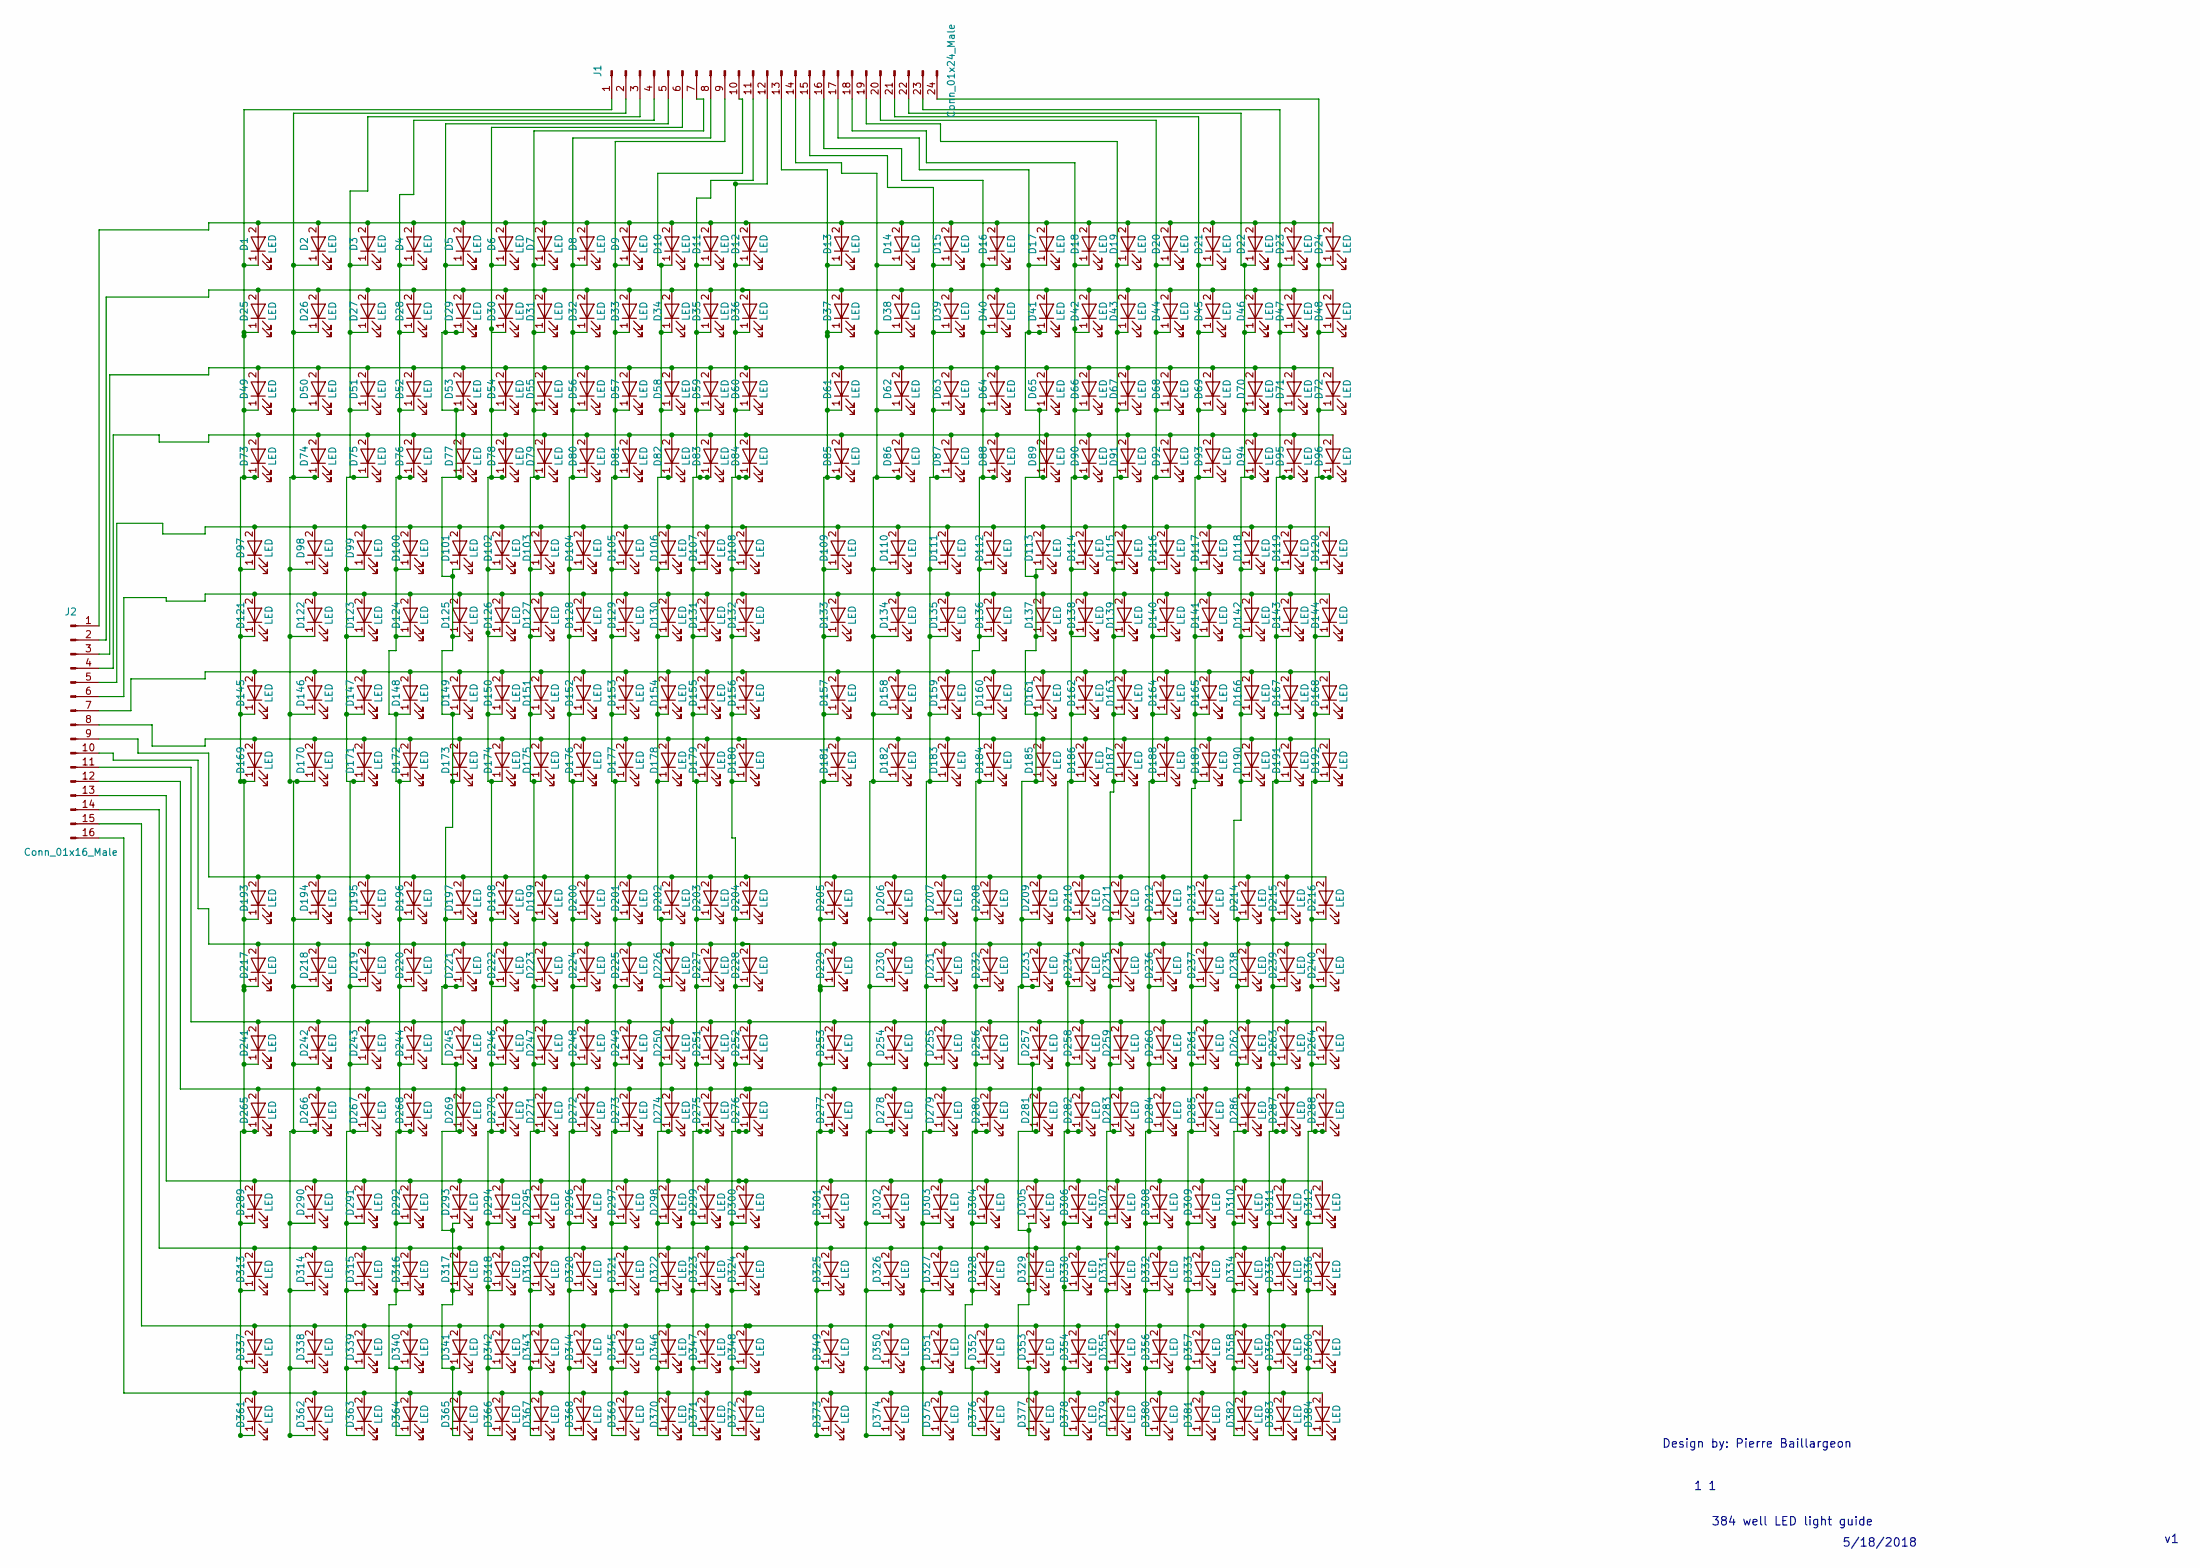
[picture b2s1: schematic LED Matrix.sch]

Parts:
D1, D2, D3, D4, D5, D6, D7, D8, D9, D10, D11, D12, D13, D14, D15, D16, D17, D18, D19, D20, D21, D22, D23, D24, D25, D26, D27, D28, D29, D30, D31, D32, D33, D34, D35, D36, D37, D38, D39, D40, D41, D42, D43, D44, D45, D46, D47, D48, D49, D50, D51, D52, D53, D54, D55, D56, D57, D58, D59, D60, D61, D62, D63, D64, D65, D66, D67, D68, D69, D70, D71, D72, D73, D74, D75, D76, D77, D78, D79, D80, D81, D82, D83, D84, D85, D86, D87, D88, D89, D90, D91, D92, D93, D94, D95, D96, D97, D98, D99, D100, D101, D102, D103, D104, D105, D106, D107, D108, D109, D110, D111, D112, D113, D114, D115, D116, D117, D118, D119, D120, D121, D122, D123, D124, D125, D126, D127, D128, D129, D130, D131, D132, D133, D134, D135, D136, D137, D138, D139, D140, D141, D142, D143, D144, D145, D146, D147, D148, D149, D150, D151, D152, D153, D154, D155, D156, D157, D158, D159, D160, D161, D162, D163, D164, D165, D166, D167, D168, D169, D170, D171, D172, D173, D174, D175, D176, D177, D178, D179, D180, D181, D182, D183, D184, D185, D186, D187, D188, D189, D190, D191, D192, D193, D194, D195, D196, D197, D198, D199, D200, D201, D202, D203, D204, D205, D206, D207, D208, D209, D210, D211, D212, D213, D214, D215, D216, D217, D218, D219, D220, D221, D222, D223, D224, D225, D226, D227, D228, D229, D230, D231, D232, D233, D234, D235, D236, D237, D238, D239, D240, D241, D242, D243, D244, D245, D246, D247, D248, D249, D250, D251, D252, D253, D254, D255, D256, D257, D258, D259, D260, D261, D262, D263, D264, D265, D266, D267, D268, D269, D270, D271, D272, D273, D274, D275, D276, D277, D278, D279, D280, D281, D282, D283, D284, D285, D286, D287, D288, D289, D290, D291, D292, D293, D294, D295, D296, D297, D298, D299, D300, D301, D302, D303, D304, D305, D306, D307, D308, D309, D310, D311, D312, D313, D314, D315, D316, D317, D318, D319, D320, D321, D322, D323, D324, D325, D326, D327, D328, D329, D330, D331, D332, D333, D334, D335, D336, D337, D338, D339, D340, D341, D342, D343, D344, D345, D346, D347, D348, D349, D350, D351, D352, D353, D354, D355, D356, D357, D358, D359, D360, D361, D362, D363, D364, D365, D366, D367, D368, D369, D370, D371, D372, D373, D374, D375, D376, D377, D378, D379, D380, D381, D382, D383, D384: LED; smallpadLED_D3.0mm
J1: Conn_01x24_Male; Pin_Header_Straight_1x24_Pitch2.54mm
J2: Conn_01x16_Male; Pin_Header_Straight_1x16_Pitch2.54mm

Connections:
unnamed: D1.1 (K), D25.1 (K), D49.1 (K), D73.1 (K), D97.1 (K), D121.1 (K), D145.1 (K), D169.1 (K), D193.1 (K), D217.1 (K), D241.1 (K), D265.1 (K), D289.1 (K), D313.1 (K), D337.1 (K), D361.1 (K), J1.1
unnamed: D1.2 (A), D2.2 (A), D3.2 (A), D4.2 (A), D5.2 (A), D6.2 (A), D7.2 (A), D8.2 (A), D9.2 (A), D10.2 (A), D11.2 (A), D12.2 (A), D13.2 (A), D14.2 (A), D15.2 (A), D16.2 (A), D17.2 (A), D18.2 (A), D19.2 (A), D20.2 (A), D21.2 (A), D22.2 (A), D23.2 (A), D24.2 (A), J2.1
unnamed: D10.1 (K), D34.1 (K), D58.1 (K), D82.1 (K), D106.1 (K), D130.1 (K), D154.1 (K), D178.1 (K), D202.1 (K), D226.1 (K), D250.1 (K), D274.1 (K), D298.1 (K), D322.1 (K), D346.1 (K), D370.1 (K), J1.10
unnamed: D25.2 (A), D26.2 (A), D27.2 (A), D28.2 (A), D29.2 (A), D30.2 (A), D31.2 (A), D32.2 (A), D33.2 (A), D34.2 (A), D35.2 (A), D36.2 (A), D37.2 (A), D38.2 (A), D39.2 (A), D40.2 (A), D41.2 (A), D42.2 (A), D43.2 (A), D44.2 (A), D45.2 (A), D46.2 (A), D47.2 (A), D48.2 (A), J2.2
unnamed: D49.2 (A), D50.2 (A), D51.2 (A), D52.2 (A), D53.2 (A), D54.2 (A), D55.2 (A), D56.2 (A), D57.2 (A), D58.2 (A), D59.2 (A), D60.2 (A), D61.2 (A), D62.2 (A), D63.2 (A), D64.2 (A), D65.2 (A), D66.2 (A), D67.2 (A), D68.2 (A), D69.2 (A), D70.2 (A), D71.2 (A), D72.2 (A), J2.3
unnamed: D73.2 (A), D74.2 (A), D75.2 (A), D76.2 (A), D77.2 (A), D78.2 (A), D79.2 (A), D80.2 (A), D81.2 (A), D82.2 (A), D83.2 (A), D84.2 (A), D85.2 (A), D86.2 (A), D87.2 (A), D88.2 (A), D89.2 (A), D90.2 (A), D91.2 (A), D92.2 (A), D93.2 (A), D94.2 (A), D95.2 (A), D96.2 (A), J2.4
unnamed: D4.1 (K), D28.1 (K), D52.1 (K), D76.1 (K), D100.1 (K), D124.1 (K), D148.1 (K), D172.1 (K), D196.1 (K), D220.1 (K), D244.1 (K), D268.1 (K), D292.1 (K), D316.1 (K), D340.1 (K), D364.1 (K), J1.4
unnamed: D97.2 (A), D98.2 (A), D99.2 (A), D100.2 (A), D101.2 (A), D102.2 (A), D103.2 (A), D104.2 (A), D105.2 (A), D106.2 (A), D107.2 (A), D108.2 (A), D109.2 (A), D110.2 (A), D111.2 (A), D112.2 (A), D113.2 (A), D114.2 (A), D115.2 (A), D116.2 (A), D117.2 (A), D118.2 (A), D119.2 (A), D120.2 (A), J2.5
unnamed: D5.1 (K), D29.1 (K), D53.1 (K), D77.1 (K), D101.1 (K), D125.1 (K), D149.1 (K), D173.1 (K), D197.1 (K), D221.1 (K), D245.1 (K), D269.1 (K), D293.1 (K), D317.1 (K), D341.1 (K), D365.1 (K), J1.5
unnamed: D6.1 (K), D30.1 (K), D54.1 (K), D78.1 (K), D102.1 (K), D126.1 (K), D150.1 (K), D174.1 (K), D198.1 (K), D222.1 (K), D246.1 (K), D270.1 (K), D294.1 (K), D318.1 (K), D342.1 (K), D366.1 (K), J1.6
unnamed: D7.1 (K), D31.1 (K), D55.1 (K), D79.1 (K), D103.1 (K), D127.1 (K), D151.1 (K), D175.1 (K), D199.1 (K), D223.1 (K), D247.1 (K), D271.1 (K), D295.1 (K), D319.1 (K), D343.1 (K), D367.1 (K), J1.7
unnamed: D8.1 (K), D32.1 (K), D56.1 (K), D80.1 (K), D104.1 (K), D128.1 (K), D152.1 (K), D176.1 (K), D200.1 (K), D224.1 (K), D248.1 (K), D272.1 (K), D296.1 (K), D320.1 (K), D344.1 (K), D368.1 (K), J1.8
unnamed: D9.1 (K), D33.1 (K), D57.1 (K), D81.1 (K), D105.1 (K), D129.1 (K), D153.1 (K), D177.1 (K), D201.1 (K), D225.1 (K), D249.1 (K), D273.1 (K), D297.1 (K), D321.1 (K), D345.1 (K), D369.1 (K), J1.9
unnamed: D11.1 (K), D35.1 (K), D59.1 (K), D83.1 (K), D107.1 (K), D131.1 (K), D155.1 (K), D179.1 (K), D203.1 (K), D227.1 (K), D251.1 (K), D275.1 (K), D299.1 (K), D323.1 (K), D347.1 (K), D371.1 (K), J1.11
unnamed: D12.1 (K), D36.1 (K), D60.1 (K), D84.1 (K), D108.1 (K), D132.1 (K), D156.1 (K), D180.1 (K), D204.1 (K), D228.1 (K), D252.1 (K), D276.1 (K), D300.1 (K), D324.1 (K), D348.1 (K), D372.1 (K), J1.12
unnamed: D13.1 (K), D37.1 (K), D61.1 (K), D85.1 (K), D109.1 (K), D133.1 (K), D157.1 (K), D181.1 (K), D205.1 (K), D229.1 (K), D253.1 (K), D277.1 (K), D301.1 (K), D325.1 (K), D349.1 (K), D373.1 (K), J1.13
unnamed: D14.1 (K), D38.1 (K), D62.1 (K), D86.1 (K), D110.1 (K), D134.1 (K), D158.1 (K), D182.1 (K), D206.1 (K), D230.1 (K), D254.1 (K), D278.1 (K), D302.1 (K), D326.1 (K), D350.1 (K), D374.1 (K), J1.14
unnamed: D15.1 (K), D39.1 (K), D63.1 (K), D87.1 (K), D111.1 (K), D135.1 (K), D159.1 (K), D183.1 (K), D207.1 (K), D231.1 (K), D255.1 (K), D279.1 (K), D303.1 (K), D327.1 (K), D351.1 (K), D375.1 (K), J1.15
unnamed: D16.1 (K), D40.1 (K), D64.1 (K), D88.1 (K), D112.1 (K), D136.1 (K), D160.1 (K), D184.1 (K), D208.1 (K), D232.1 (K), D256.1 (K), D280.1 (K), D304.1 (K), D328.1 (K), D352.1 (K), D376.1 (K), J1.16
unnamed: D17.1 (K), D41.1 (K), D65.1 (K), D89.1 (K), D113.1 (K), D137.1 (K), D161.1 (K), D185.1 (K), D209.1 (K), D233.1 (K), D257.1 (K), D281.1 (K), D305.1 (K), D329.1 (K), D353.1 (K), D377.1 (K), J1.17
unnamed: D18.1 (K), D42.1 (K), D66.1 (K), D90.1 (K), D114.1 (K), D138.1 (K), D162.1 (K), D186.1 (K), D210.1 (K), D234.1 (K), D258.1 (K), D282.1 (K), D306.1 (K), D330.1 (K), D354.1 (K), D378.1 (K), J1.18
unnamed: D19.1 (K), D43.1 (K), D67.1 (K), D91.1 (K), D115.1 (K), D139.1 (K), D163.1 (K), D187.1 (K), D211.1 (K), D235.1 (K), D259.1 (K), D283.1 (K), D307.1 (K), D331.1 (K), D355.1 (K), D379.1 (K), J1.19
unnamed: D20.1 (K), D44.1 (K), D68.1 (K), D92.1 (K), D116.1 (K), D140.1 (K), D164.1 (K), D188.1 (K), D212.1 (K), D236.1 (K), D260.1 (K), D284.1 (K), D308.1 (K), D332.1 (K), D356.1 (K), D380.1 (K), J1.20
unnamed: D21.1 (K), D45.1 (K), D69.1 (K), D93.1 (K), D117.1 (K), D141.1 (K), D165.1 (K), D189.1 (K), D213.1 (K), D237.1 (K), D261.1 (K), D285.1 (K), D309.1 (K), D333.1 (K), D357.1 (K), D381.1 (K), J1.21
unnamed: D22.1 (K), D46.1 (K), D70.1 (K), D94.1 (K), D118.1 (K), D142.1 (K), D166.1 (K), D190.1 (K), D214.1 (K), D238.1 (K), D262.1 (K), D286.1 (K), D310.1 (K), D334.1 (K), D358.1 (K), D382.1 (K), J1.22
unnamed: D23.1 (K), D47.1 (K), D71.1 (K), D95.1 (K), D119.1 (K), D143.1 (K), D167.1 (K), D191.1 (K), D215.1 (K), D239.1 (K), D263.1 (K), D287.1 (K), D311.1 (K), D335.1 (K), D359.1 (K), D383.1 (K), J1.23
unnamed: D24.1 (K), D48.1 (K), D72.1 (K), D96.1 (K), D120.1 (K), D144.1 (K), D168.1 (K), D192.1 (K), D216.1 (K), D240.1 (K), D264.1 (K), D288.1 (K), D312.1 (K), D336.1 (K), D360.1 (K), D384.1 (K), J1.24
unnamed: D121.2 (A), D122.2 (A), D123.2 (A), D124.2 (A), D125.2 (A), D126.2 (A), D127.2 (A), D128.2 (A), D129.2 (A), D130.2 (A), D131.2 (A), D132.2 (A), D133.2 (A), D134.2 (A), D135.2 (A), D136.2 (A), D137.2 (A), D138.2 (A), D139.2 (A), D140.2 (A), D141.2 (A), D142.2 (A), D143.2 (A), D144.2 (A), J2.6
unnamed: D2.1 (K), D26.1 (K), D50.1 (K), D74.1 (K), D98.1 (K), D122.1 (K), D146.1 (K), D170.1 (K), D194.1 (K), D218.1 (K), D242.1 (K), D266.1 (K), D290.1 (K), D314.1 (K), D338.1 (K), D362.1 (K), J1.2
unnamed: D3.1 (K), D27.1 (K), D51.1 (K), D75.1 (K), D99.1 (K), D123.1 (K), D147.1 (K), D171.1 (K), D195.1 (K), D219.1 (K), D243.1 (K), D267.1 (K), D291.1 (K), D315.1 (K), D339.1 (K), D363.1 (K), J1.3
unnamed: D145.2 (A), D146.2 (A), D147.2 (A), D148.2 (A), D149.2 (A), D150.2 (A), D151.2 (A), D152.2 (A), D153.2 (A), D154.2 (A), D155.2 (A), D156.2 (A), D157.2 (A), D158.2 (A), D159.2 (A), D160.2 (A), D161.2 (A), D162.2 (A), D163.2 (A), D164.2 (A), D165.2 (A), D166.2 (A), D167.2 (A), D168.2 (A), J2.7
unnamed: D169.2 (A), D170.2 (A), D171.2 (A), D172.2 (A), D173.2 (A), D174.2 (A), D175.2 (A), D176.2 (A), D177.2 (A), D178.2 (A), D179.2 (A), D180.2 (A), D181.2 (A), D182.2 (A), D183.2 (A), D184.2 (A), D185.2 (A), D186.2 (A), D187.2 (A), D188.2 (A), D189.2 (A), D190.2 (A), D191.2 (A), D192.2 (A), J2.8
unnamed: D193.2 (A), D194.2 (A), D195.2 (A), D196.2 (A), D197.2 (A), D198.2 (A), D199.2 (A), D200.2 (A), D201.2 (A), D202.2 (A), D203.2 (A), D204.2 (A), D205.2 (A), D206.2 (A), D207.2 (A), D208.2 (A), D209.2 (A), D210.2 (A), D211.2 (A), D212.2 (A), D213.2 (A), D214.2 (A), D215.2 (A), D216.2 (A), J2.9
unnamed: D217.2 (A), D218.2 (A), D219.2 (A), D220.2 (A), D221.2 (A), D222.2 (A), D223.2 (A), D224.2 (A), D225.2 (A), D226.2 (A), D227.2 (A), D228.2 (A), D229.2 (A), D230.2 (A), D231.2 (A), D232.2 (A), D233.2 (A), D234.2 (A), D235.2 (A), D236.2 (A), D237.2 (A), D238.2 (A), D239.2 (A), D240.2 (A), J2.10
unnamed: D241.2 (A), D242.2 (A), D243.2 (A), D244.2 (A), D245.2 (A), D246.2 (A), D247.2 (A), D248.2 (A), D249.2 (A), D250.2 (A), D251.2 (A), D252.2 (A), D253.2 (A), D254.2 (A), D255.2 (A), D256.2 (A), D257.2 (A), D258.2 (A), D259.2 (A), D260.2 (A), D261.2 (A), D262.2 (A), D263.2 (A), D264.2 (A), J2.11
unnamed: D265.2 (A), D266.2 (A), D267.2 (A), D268.2 (A), D269.2 (A), D270.2 (A), D271.2 (A), D272.2 (A), D273.2 (A), D274.2 (A), D275.2 (A), D276.2 (A), D277.2 (A), D278.2 (A), D279.2 (A), D280.2 (A), D281.2 (A), D282.2 (A), D283.2 (A), D284.2 (A), D285.2 (A), D286.2 (A), D287.2 (A), D288.2 (A), J2.12
unnamed: D289.2 (A), D290.2 (A), D291.2 (A), D292.2 (A), D293.2 (A), D294.2 (A), D295.2 (A), D296.2 (A), D297.2 (A), D298.2 (A), D299.2 (A), D300.2 (A), D301.2 (A), D302.2 (A), D303.2 (A), D304.2 (A), D305.2 (A), D306.2 (A), D307.2 (A), D308.2 (A), D309.2 (A), D310.2 (A), D311.2 (A), D312.2 (A), J2.13
unnamed: D313.2 (A), D314.2 (A), D315.2 (A), D316.2 (A), D317.2 (A), D318.2 (A), D319.2 (A), D320.2 (A), D321.2 (A), D322.2 (A), D323.2 (A), D324.2 (A), D325.2 (A), D326.2 (A), D327.2 (A), D328.2 (A), D329.2 (A), D330.2 (A), D331.2 (A), D332.2 (A), D333.2 (A), D334.2 (A), D335.2 (A), D336.2 (A), J2.14
unnamed: D337.2 (A), D338.2 (A), D339.2 (A), D340.2 (A), D341.2 (A), D342.2 (A), D343.2 (A), D344.2 (A), D345.2 (A), D346.2 (A), D347.2 (A), D348.2 (A), D349.2 (A), D350.2 (A), D351.2 (A), D352.2 (A), D353.2 (A), D354.2 (A), D355.2 (A), D356.2 (A), D357.2 (A), D358.2 (A), D359.2 (A), D360.2 (A), J2.15
unnamed: D361.2 (A), D362.2 (A), D363.2 (A), D364.2 (A), D365.2 (A), D366.2 (A), D367.2 (A), D368.2 (A), D369.2 (A), D370.2 (A), D371.2 (A), D372.2 (A), D373.2 (A), D374.2 (A), D375.2 (A), D376.2 (A), D377.2 (A), D378.2 (A), D379.2 (A), D380.2 (A), D381.2 (A), D382.2 (A), D383.2 (A), D384.2 (A), J2.16

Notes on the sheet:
384 well LED light guide
5/18/2018
Design by: Pierre Baillargeon
